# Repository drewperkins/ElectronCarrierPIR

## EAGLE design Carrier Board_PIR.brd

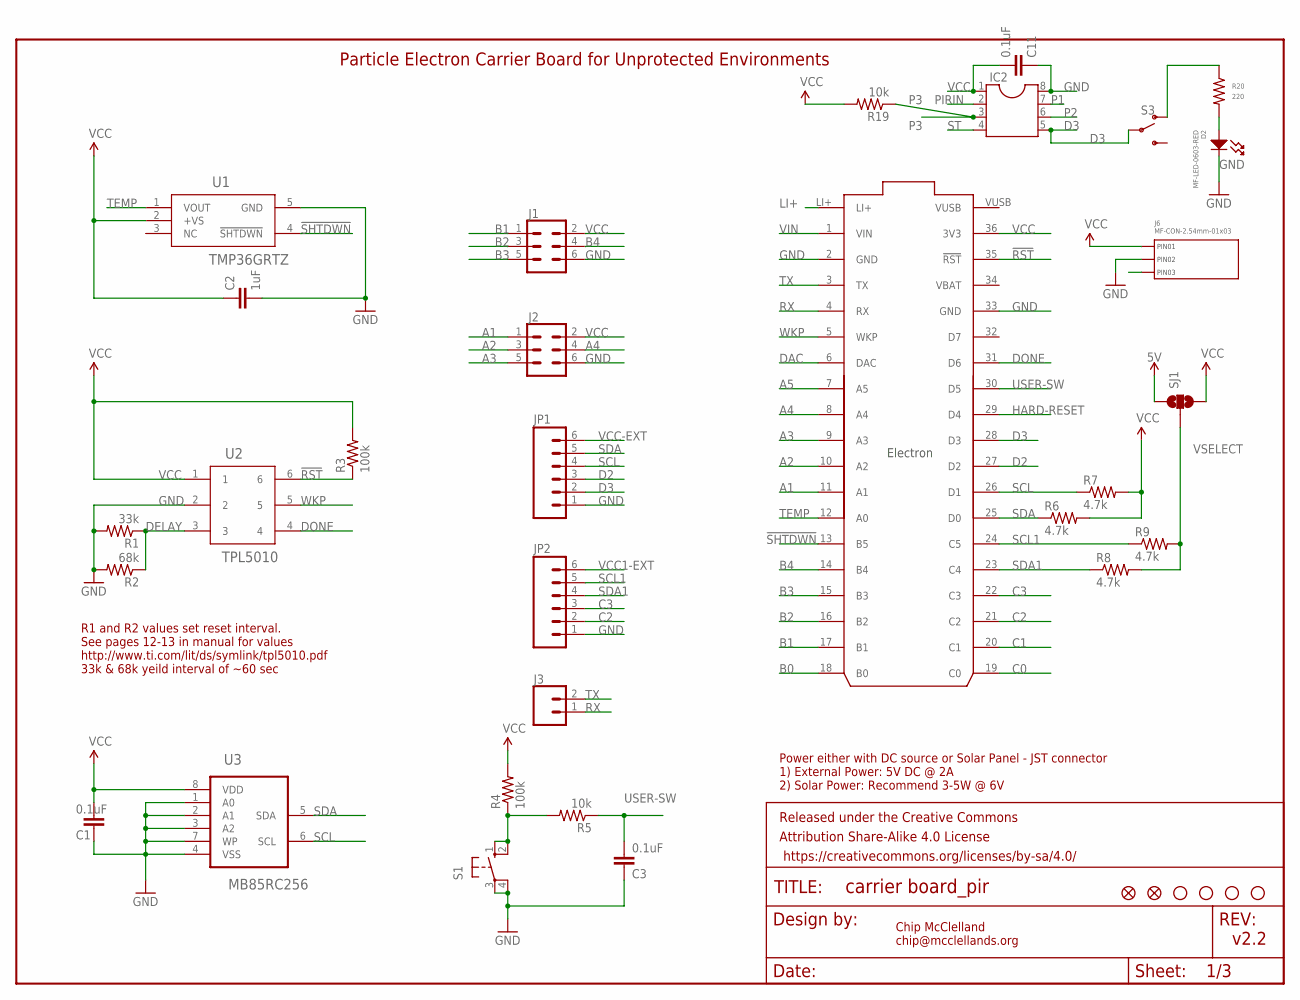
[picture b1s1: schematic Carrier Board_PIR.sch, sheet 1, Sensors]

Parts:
C1, C3, C11: 0.1uF; 0805
C2: 1uF; 0805
D2: MF-LED-0603-RED; LED0603
FD1, FD2: FIDUCIALUFIDUCIAL; FIDUCIAL-MICRO
FRAME1: FRAME-LETTER; CREATIVE_COMMONS
IC2: DIL8S; SOCKET-08
J1, J2: CONN_03X22X3_SILK_MALE_PTH; 2X3
J3: CONN_02; 1X02
J6: MF-CON-2.54mm-01x03; PTH_2.54MM_01X03
JP1, JP2: M06LOCK; 1X06_LOCK
JP3, JP4, JP5, JP6: STAND-OFF
R1: 33k; 0805
R2: 68k; 0805
R3, R4: 100k; 0805
R5, R19: 10k; 0805
R6, R7, R8, R9: 4.7k; 0805
R20: 220; R0603
S1: 10-XX; B3F-10XX
S3: SWITCH-SPDT-SMD-RIGHT-ANGLE; SWITCH_SPST_SMD_A
SJ1: SOLDERJUMPER_2WAYPASTE1&2; SJ_3_PASTE1&2
U1: TMP36GRTZ; RJ_5
U2: TPL5010; TSOT-23
U3: MB85RC256; SOIC127P600X175-8N
U4: Particle Electron; ELECTON-PWR-PINS

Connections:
5V: SJ1.1; also elsewhere on the board
!RST: R3.1, U2.6, U4.35 (!RST)
!SHTDWN: U1.4 (!SHTDWN), U4.13 (B5)
A1: J2.1, U4.11 (A1)
A2: J2.3, U4.10 (A2)
A3: J2.5, U4.9 (A3)
A4: J2.4, U4.8 (A4)
A5: U4.7 (A5)
B0: U4.18 (B0)
B1: J1.1, U4.17 (B1)
B2: J1.3, U4.16 (B2)
B3: J1.5, U4.15 (B3)
B4: J1.4, U4.14 (B4)
C0: U4.19 (C0)
C1: U4.20 (C1)
C2: JP2.2, U4.21 (C2); also elsewhere on the board
C3: JP2.3, U4.22 (C3); also elsewhere on the board
D2: JP1.3, U4.27 (D2); also elsewhere on the board
D3: IC2.5, JP1.2, S3.2, U4.28 (D3); also elsewhere on the board
DAC: U4.6 (DAC)
DELAY: R1.1, R2.1, U2.3
DONE: U2.4, U4.31 (D6)
GND: C1.2, C2.2, C3.2, C11.2, D2.CATHODE, IC2.8, J1.6, J2.6, J6.P$2 (PIN2), JP1.1, JP2.1, R1.2, R2.2, S1.3, S1.4 (P1), U1.5 (GND), U2.2, U3.1 (A0), U3.2 (A1), U3.3 (A2), U3.4 (VSS), U3.7 (WP), U4.2 (GND), U4.33 (GND); also elsewhere on the board
HARD-RESET: U4.29 (D4); also elsewhere on the board
LI+: U4.LI+; also elsewhere on the board
unnamed: R4.1, R5.2, S1.1 (S), S1.2 (S1)
unnamed: R20.P$1, S3.1 (O)
unnamed: D2.ANODE, R20.P$2
P1: IC2.7
P2: IC2.6
P3: IC2.3, R19.1
PIRIN: IC2.2, J6.P$3 (PIN3)
RX: J3.1, U4.4 (RX)
SCL: JP1.4, R7.1, U3.6 (SCL), U4.26 (D1); also elsewhere on the board
SCL1: JP2.5, R9.1, U4.24 (C5); also elsewhere on the board
SDA: JP1.5, R6.1, U3.5 (SDA), U4.25 (D0); also elsewhere on the board
SDA1: JP2.4, R8.1, U4.23 (C4); also elsewhere on the board
ST: IC2.4
TEMP: U1.1 (VOUT), U4.12 (A0)
TX: J3.2, U4.3 (TX)
USER-SW: C3.1, R5.1, U4.30 (D5)
VBAT: U4.34 (VBAT)
VCC: C1.1, C2.1, C11.1, IC2.1, J1.2, J2.2, J6.P$1 (PIN1), R3.2, R4.2, R6.2, R7.2, R19.2, SJ1.3, U1.2 (+VS), U2.1, U3.8 (VDD), U4.36 (3V3); also elsewhere on the board
VCC1-EXT: JP2.6; also elsewhere on the board
VCC-EXT: JP1.6; also elsewhere on the board
VIN: U4.1 (VIN); also elsewhere on the board
VSELECT: R8.2, R9.2, SJ1.2; also elsewhere on the board
WKP: U2.5, U4.5 (WKP)

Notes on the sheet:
Chip McClelland chip@mcclellands.org
v2.2
Power either with DC source or Solar Panel - JST connector 1) External Power: 5V DC @ 2A 2) Solar Power: Recommend 3-5W @ 6V
Particle Electron Carrier Board for Unprotected Environments
R1 and R2 values set reset interval. See pages 12-13 in manual for values http://www.ti.com/lit/ds/symlink/tpl5010.pdf 33k & 68k yeild interval of ~60 sec

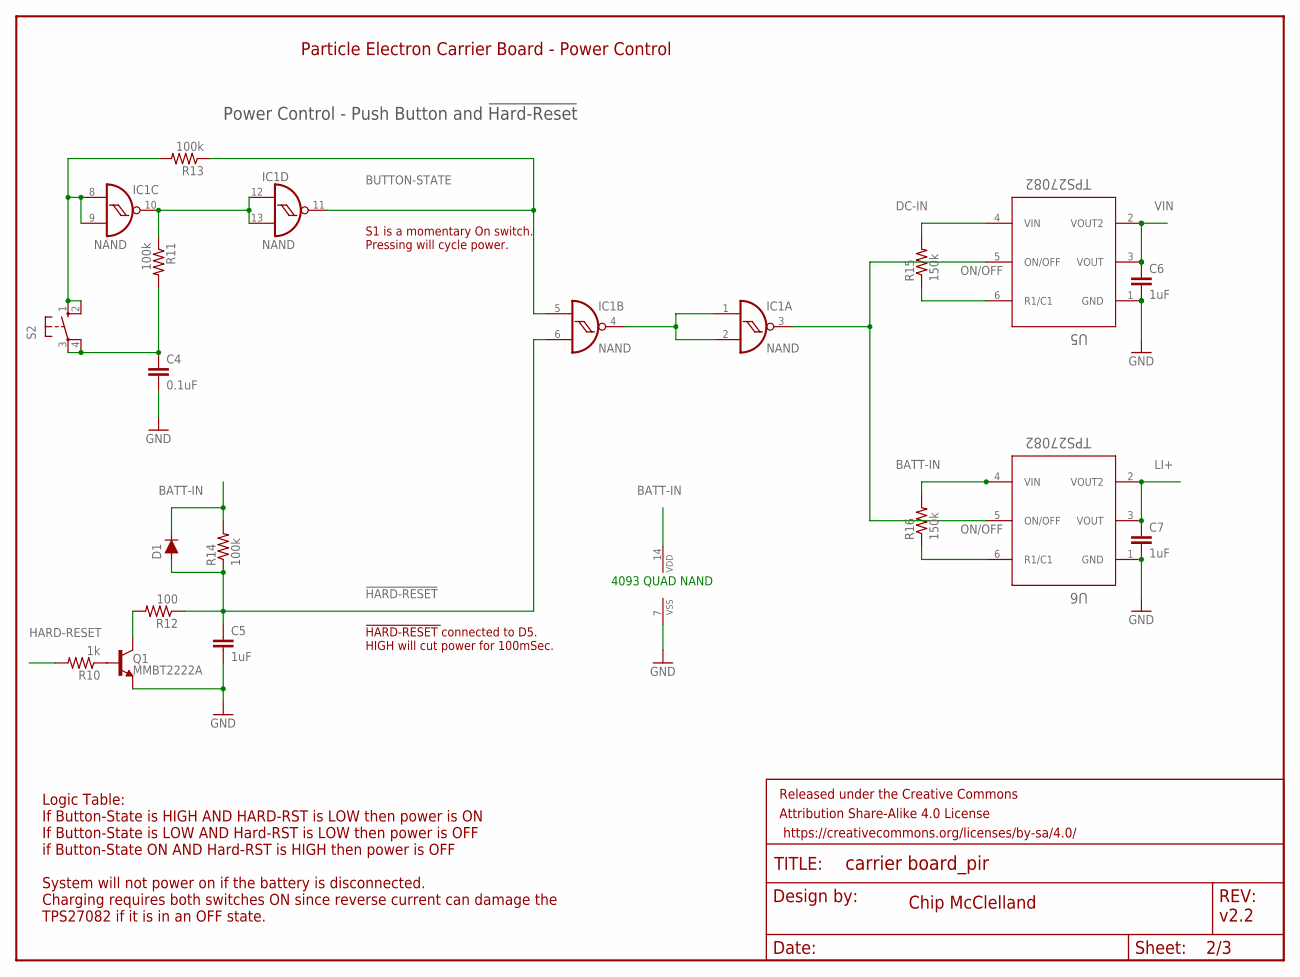
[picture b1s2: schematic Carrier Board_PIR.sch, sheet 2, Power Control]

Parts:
C4: 0.1uF; 0805
C5, C6, C7: 1uF; 0805
D1: DIODE-BAS16J; SOD-323
FRAME2: FRAME-LETTER; CREATIVE_COMMONS
IC1: NAND; MC14093B-TSSOP14
Q1: MMBT2222A; SOT23-3
R10: 1k; 0805
R11, R13, R14: 100k; 0805
R12: 100; 0805
R15, R16: 150k; 0805
S2: 40-XX-ROUND; B3F-40XX-ROUND
U5, U6: TPS27082; TSOT-23

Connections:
!HARD-RESET: C5.1, D1.A, IC1.6 (I1), R12.1, R14.1
BATT-IN: D1.C, IC1.14 (VDD), R14.2, R16.2, U6.4 (VIN); also elsewhere on the board
BUTTON-STATE: IC1.5 (I0), IC1.11 (O), R13.1
DC-IN: R15.2, U5.4 (VIN); also elsewhere on the board
GND: C4.2, C5.2, C6.2, C7.2, IC1.7 (VSS), Q1.2 (E), U5.1 (GND), U6.1 (GND); also elsewhere on the board
HARD-RESET: R10.2; also elsewhere on the board
LI+: C7.1, U6.2 (VOUT2), U6.3 (VOUT); also elsewhere on the board
unnamed: IC1.1 (I0), IC1.2 (I1), IC1.4 (O)
unnamed: IC1.10 (O), IC1.12 (I0), IC1.13 (I1), R11.1
unnamed: R15.1, U5.6 (R1/C1)
unnamed: Q1.1 (B), R10.1
unnamed: R16.1, U6.6 (R1/C1)
unnamed: Q1.3 (C), R12.2
unnamed: C4.1, R11.2, S2.3, S2.4 (P1)
unnamed: IC1.8 (I0), IC1.9 (I1), R13.2, S2.1 (S), S2.2 (S1)
ON/OFF: IC1.3 (O), U5.5 (ON/OFF), U6.5 (ON/OFF)
VIN: C6.1, U5.2 (VOUT2), U5.3 (VOUT); also elsewhere on the board

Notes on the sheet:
Particle Electron Carrier Board - Power Control
4093 QUAD NAND
Power Control - Push Button and !Hard-Reset
Chip McClelland
v2.2
Logic Table: If Button-State is HIGH AND HARD-RST is LOW then power is ON If Button-State is LOW AND Hard-RST is LOW then power is OFF if Button-State ON AND Hard-RST is HIGH then power is OFF System will not power on if the battery is disconnected. Charging requires both switches ON since reverse 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
!HARD-RESET !connected to D5. HIGH will cut power for 100mSec.
S1 is a momentary On switch. Pressing will cycle power.

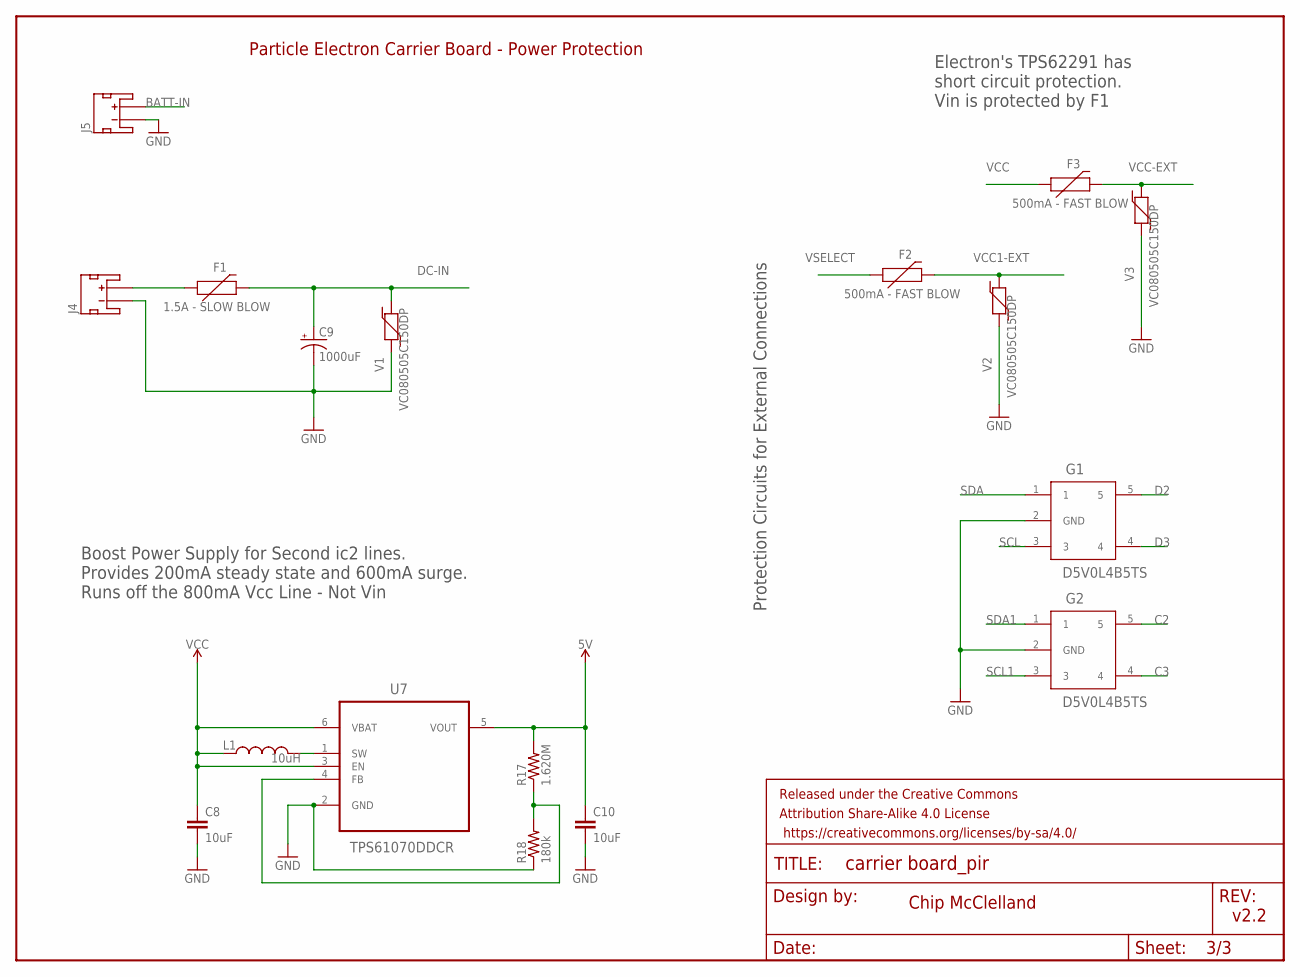
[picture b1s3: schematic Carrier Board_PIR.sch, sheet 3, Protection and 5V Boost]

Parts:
C8, C10: 10uF; 0805
C9: 1000uF; PANASONIC_G
F1: 1.5A - SLOW BLOW; 1206
F2, F3: 500mA - FAST BLOW; 1206
FRAME3: FRAME-LETTER; CREATIVE_COMMONS
G1, G2: D5V0L4B5TS; SOT-23-5
J4: 5V @ 2A; JST-2-SMD
J5: JST_2MM_MALE; JST-2-SMD
L1: 10uH; SDR0403
R17: 1.620M; 0805
R18: 180k; 0805
U7: TPS61070DDCR; SOT95P280X110-6N
V1, V2, V3: VC080505C150DP; 0805

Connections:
5V: C10.1, R17.2, U7.5 (VOUT); also elsewhere on the board
BATT-IN: J5.2 (+); also elsewhere on the board
C2: G2.5; also elsewhere on the board
C3: G2.4; also elsewhere on the board
D2: G1.5; also elsewhere on the board
D3: G1.4; also elsewhere on the board
DC-IN: C9.+, F1.2, V1.2; also elsewhere on the board
DC-IN-EXT: F1.1, J4.2 (+)
GND: C8.2, C9.-, C10.2, G1.2 (GND), G2.2 (GND), J4.1 (-), J5.1 (-), R18.1, U7.2 (GND), V1.1, V2.1, V3.1; also elsewhere on the board
unnamed: R17.1, R18.2, U7.4 (FB)
SCL: G1.3; also elsewhere on the board
SCL1: G2.3; also elsewhere on the board
SDA: G1.1; also elsewhere on the board
SDA1: G2.1; also elsewhere on the board
SW: L1.P$2 (2), U7.1 (SW)
VCC: C8.1, F3.1, L1.P$1 (1), U7.3 (EN), U7.6 (VBAT); also elsewhere on the board
VCC1-EXT: F2.2, V2.2; also elsewhere on the board
VCC-EXT: F3.2, V3.2; also elsewhere on the board
VSELECT: F2.1; also elsewhere on the board

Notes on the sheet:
Protection Circuits for External Connections
Electron's TPS62291 has short circuit protection. Vin is protected by F1
Boost Power Supply for Second ic2 lines. Provides 200mA steady state and 600mA surge. Runs off the 800mA Vcc Line - Not Vin
Chip McClelland
v2.2
Particle Electron Carrier Board - Power Protection

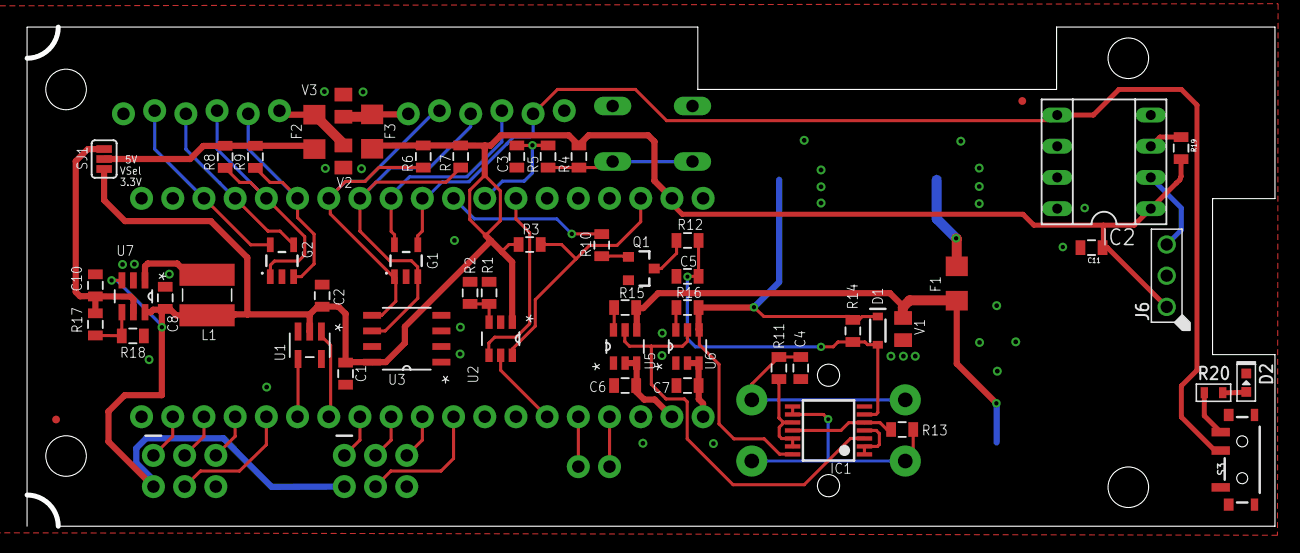
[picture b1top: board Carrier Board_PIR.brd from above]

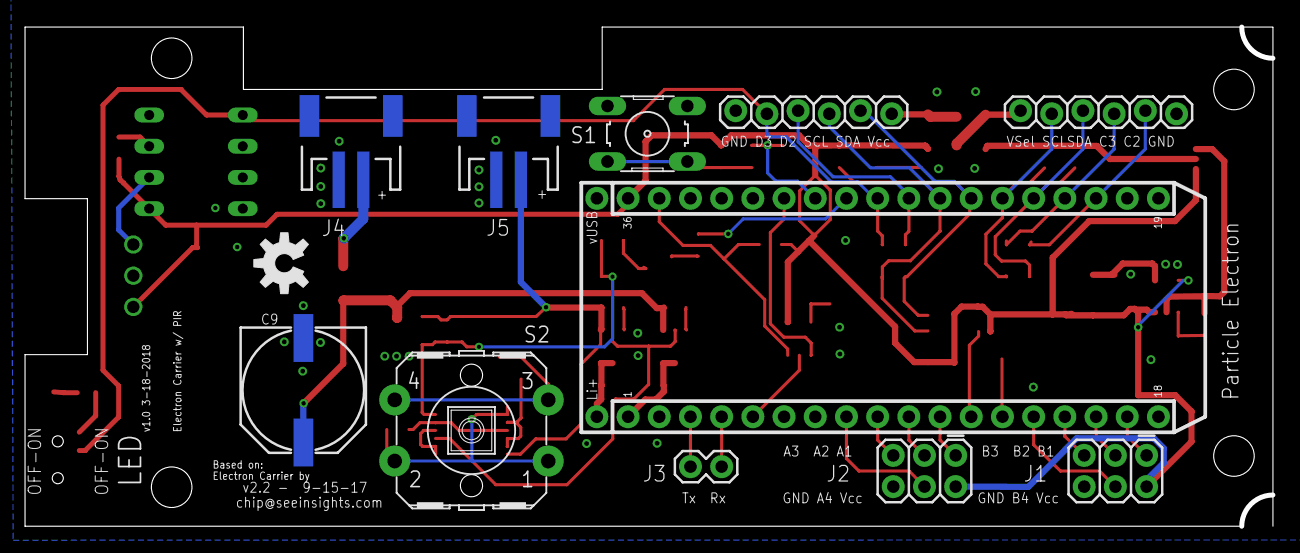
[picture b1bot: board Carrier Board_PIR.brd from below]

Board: 2 copper layers, 101.4 x 40.6 mm, 74 parts (12 on the bottom side), 55 nets.

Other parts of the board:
U$2: OSHW-LOGO-M

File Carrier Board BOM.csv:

Part,Value,Device,Package,Description,DIST,DIST_ID
C1,0.1uF,CAP0805,0805,Capacitor,DIGIKEY,
C2,1uF,CAP0805,0805,Capacitor,DIGIKEY,
C3,0.1uF,CAP0805,0805,Capacitor,DIGIKEY,
C4,0.1uF,CAP0805,0805,Capacitor,DIGIKEY,
C5,1uF,CAP0805,0805,Capacitor,DIGIKEY,
C6,1uF,CAP0805,0805,Capacitor,DIGIKEY,
C7,1uF,CAP0805,0805,Capacitor,DIGIKEY,
C8,10uF,CAP0805,0805,Capacitor,DIGIKEY,
C9,1000uF,CAP_POLG,PANASONIC_G,Capacitor Polarized,DIGIKEY,P15087CT-ND
C10,10uF,CAP0805,0805,Capacitor,DIGIKEY,SRN4026-100MCT-ND
D1,Diode,DIODE-BAS16J,SOD-323,DIODE SCHOTTKY 40V 1A SOD323A,DIGIKEY,893-1188-1-ND
F1,1.5A - SLOW BLOW,Fuse,1206,FUSE BRD MNT 1.5A 63VAC/VDC 1206,DIGIKEY,F2569CT-ND
F2,500mA - FAST BLOW,Fuse,1206,FUSE BOARD MOUNT 500MA 63VAC/VDC,DIGIKEY,F3156CT-ND
F3,500mA - FAST BLOW,Fuse,1206,FUSE BOARD MOUNT 500MA 63VAC/VDC,DIGIKEY,F3156CT-ND
G1,D5V0L4B5TS,D5V0L4B5TS,SOT-23-5,4 CHANNEL LOW CAPACITANCE BI-DIRECTIONAL TVS ARRAY,DIGIKEY,D5V0L4B5TS-7DICT-ND
G2,D5V0L4B5TS,D5V0L4B5TS,SOT-23-5,4 CHANNEL LOW CAPACITANCE BI-DIRECTIONAL TVS ARRAY,DIGIKEY,D5V0L4B5TS-7DICT-ND
IC1,NAND,4093DT,MC14093B-TSSOP14,Quad 2-input NAND schmitt trigger,DIGIKEY,
J1,Analog/Digital IO,"0.1"" Male Header",2X3,Header,DIGIKEY,
J2,Analog/Digital IO,"0.1"" Male Header",2X3,Header,DIGIKEY,
J3,Serial Header,"0.1"" Male Header",1X02,Header,DIGIKEY,
J4,5V @ 2A,JST_2MM_MALE,JST-2-SMD,JST 2MM MALE RA CONNECTOR,DIGIKEY,455-1749-1-ND
J5,LiPo Connector,JST_2MM_MALE,JST-2-SMD,JST 2MM MALE RA CONNECTOR,DIGIKEY,455-1749-1-ND
JP1,i2c Header,"0.1"" Male Header",1X06_LOCK,Header,DIGIKEY,
JP2,i2c Header,"0.1"" Male Header",1X06_LOCK,Header,DIGIKEY,
L1,10uH,INDUCTORSDR0403-560KL,SDR0403,Inductors,DIGIKEY,SDR0403-560KLCT-ND
Q1,MMBT2222A,TRANS_NPN-MMBT2222AL,SOT23-3,NPN transistor,DIGIKEY,MMBT2222ALT1GOSCT-ND
R1,33k,125mW 1% Resistor,0805,Resistor,DIGIKEY,
R2,68k,125mW 1% Resistor,0805,Resistor,DIGIKEY,
R3,100k,125mW 1% Resistor,0805,Resistor,DIGIKEY,
R4,100k,125mW 1% Resistor,0805,Resistor,DIGIKEY,
R5,10k,125mW 1% Resistor,0805,Resistor,DIGIKEY,
R6,4.7k,125mW 1% Resistor,0805,Resistor,DIGIKEY,
R7,4.7k,125mW 1% Resistor,0805,Resistor,DIGIKEY,
R8,4.7k,125mW 1% Resistor,0805,Resistor,DIGIKEY,
R9,4.7k,125mW 1% Resistor,0805,Resistor,DIGIKEY,
R10,1k,125mW 1% Resistor,0805,Resistor,DIGIKEY,
R11,100k,125mW 1% Resistor,0805,Resistor,DIGIKEY,
R12,100,125mW 1% Resistor,0805,Resistor,DIGIKEY,
R13,100k,125mW 1% Resistor,0805,Resistor,DIGIKEY,
R14,100k,125mW 1% Resistor,0805,Resistor,DIGIKEY,
R15,150k,125mW 1% Resistor,0805,Resistor,DIGIKEY,
R16,150k,125mW 1% Resistor,0805,Resistor,DIGIKEY,
R17,1.620M,125mW 1% Resistor,0805,Resistor,DIGIKEY,
R18,180k,125mW 1% Resistor,0805,Resistor,DIGIKEY,
S1,User Switch,10-XX,B3F-1070,OMRON SWITCH,DIGIKEY,SW406-ND
S2,Power Switch,40-XX-ROUND,B3F-40XX-ROUND,OMRON SWITCH,DIGIKEY,SW411-ND
U1,TMP36GRTZ,TMP36GRTZ-REEL7,SOT-23-5,SENSOR TEMP ANLG VOLT SOT-23-5,DIGIKEY,TMP36GRTZ-REEL7TR-ND
U2,TPL5010,TPL5010,TSOT-23,Watchdog Timer Chip,DIGIKEY,296-44392-1-ND
U3,MB85RC256,MB85RC128PNF-G-JNE1,SOIC127P600X175-8N,Memory FRAM,DIGIKEY,865-1261-1-ND
U4,Particle Electron,ELECTRON-PWR-PINS,ELECTON-PWR-PINS,This is a Electron pinout with the two power pins populated,DIGIKEY,
U5,TPS27082,TPS27082,TSOT-23,TI TPS27082 Single High-Side On-Off Switch,DIGIKEY,
U6,TPS27082,TPS27082,TSOT-23,TI TPS27082 Single High-Side On-Off Switch,DIGIKEY,
U7,TPS61070DDCR,TPS61070DDCR,TSOT-23-6,SYNCHRONOUS BOOST CONVERTER,DIGIKEY,296-21523-1-ND
V1,VC080505C150DP ,VARISTOR,0805,VARISTOR 8.5V 120A 0805,DIGIKEY,478-2507-1-ND
V2,VC080505C150DP ,VARISTOR,0805,VARISTOR 8.5V 120A 0805,DIGIKEY,478-2507-1-ND
V3,VC080505C150DP ,VARISTOR,0805,VARISTOR 8.5V 120A 0805,DIGIKEY,478-2507-1-ND

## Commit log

2018-03-20 Version 1
    Created repository

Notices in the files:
parts and their libraries:
SparkFun-Aesthetics: Licensing: Creative Commons ShareAlike 4.0 International - https://creativecommons.org/licenses/by-sa/4.0
SparkFun-Aesthetics: Released under the Creative Commons Attribution Share-Alike 4.0 License
SparkFun-Aesthetics: https://creativecommons.org/licenses/by-sa/4.0
